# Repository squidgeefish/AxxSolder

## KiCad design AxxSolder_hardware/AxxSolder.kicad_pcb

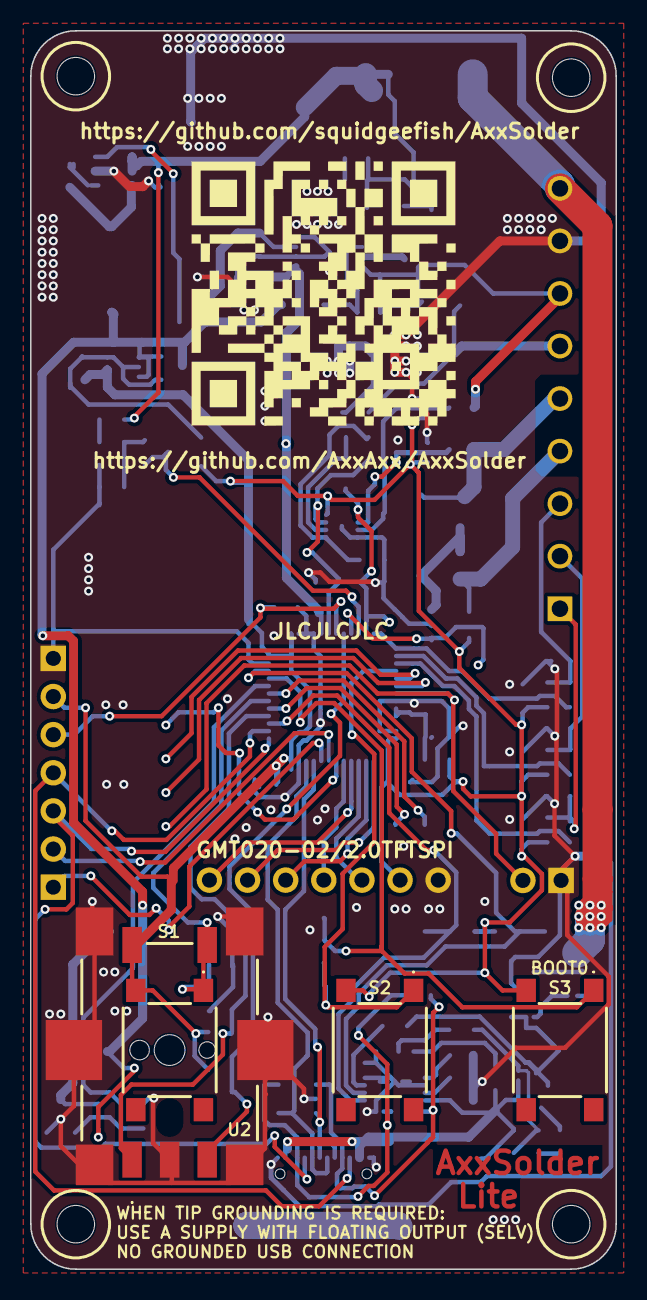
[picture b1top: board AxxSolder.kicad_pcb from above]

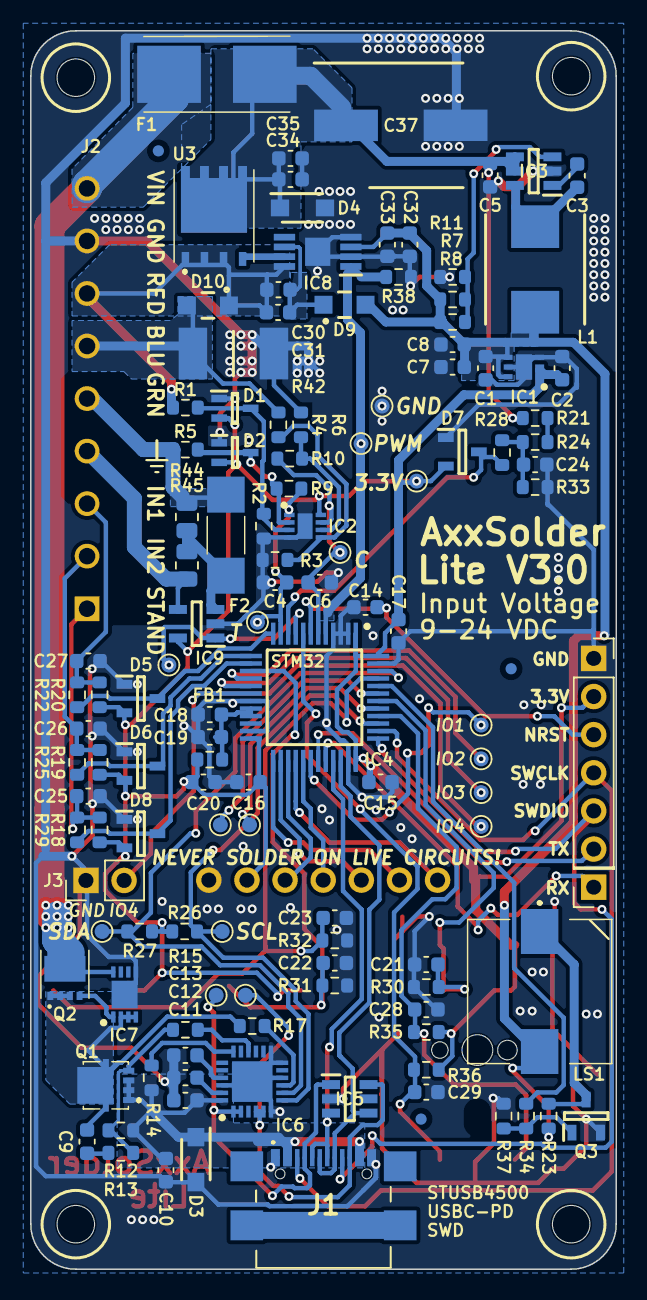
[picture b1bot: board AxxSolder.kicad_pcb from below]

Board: 2 copper layers, 39.0 x 82.5 mm, 137 parts (128 on the bottom side), 68 nets.

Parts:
C1, C2, C5, C7, C8, C10, C11, C12, C13, C19, C20, C30, C31, C32, C34, C35: 10u; C_0603_1608Metric
C3, C9, C14, C15, C16, C17, C18, C21, C22, C23, C24, C25, C26, C27, C28, C29, C33: 100n; C_0603_1608Metric
C4, C6: 1n; C_0603_1608Metric
C37: 220u; CAPAE830X1050N
D1, D2: BAV199WQ-7; SOT65P210X110-3N
D3, D4: SMF4L24AT1G; SODFL3619X98N
D5, D6, D7, D8: BAT54S; SOT95P230X110-3N
D9, D10: PMEG6020ER; PMEG6020ER115
F1: 0154007.DR; 0154100DR
F2: SF-2410FP100W-2; SF2410FP100W2
FB1: BLM18HE601SN1D; R_0603_1608Metric
FID1, FID2, FID3: Fiducial; Fiducial_0.75mm_Mask1.5mm
H1, H2, H3, H4: MountingHole; MountingHole_2.5mm
IC1: TLV76733DRVR; SON65P200X200X80-7N
IC2: OPA2387DSGT; SON50P200X200X80-9N
IC3: LMR54406DBVR; SOT95P280X145-6N
IC4: STM32G431CBT6; QFP50P900X900X160-48N
IC5: TPD4E1U06DBVR; SOT95P280X145-6N
IC6: STUSB4500QTR; QFN50P400X400X100-25N-D
IC7: MAX16171ATA_VY+T; SON50P300X200X80-9N
IC8: LTC4440AHMS8E; SOP65P490X110-9N
IC9: INA281A5QDBVRQ1; SOT95P280X145-5N
J1: USB4110-GF-A; USB4110GFA
J2: 691243110009
J3: TSW-102-07-T-S; PinHeader_1x02_P2.54mm_Vertical
J4: 61300611821; RHDR6W97P0X254_1X6_1574X250X865P
L1: SRP7028CC-150M; INDPM7366X300N
LS1: CMI-9653S-SMT-TR; CMI9653SSMTTR
Q1: STL9P3LLH6; STL20N6F7
Q2: STL10N3LLH5
Q3: 2N7002NXAKR; SOT95P230X110-3N
R1, R5, R14, R17: 1k5; R_0603_1608Metric
R2, R7, R8, R9: 360k; R_0603_1608Metric
R3, R10: 220k; R_0603_1608Metric
R4, R6, R18, R19, R20, R22, R23, R25, R26, R27, R28, R29, R30, R31, R32, R33, R35, R36, R37, R38: 4k7; R_0603_1608Metric
R11, R12, R15, R21, R24: 22k; R_0603_1608Metric
R13, R34: 100; R_0603_1608Metric
R42: 5m; RESC6432X89N
R44: 1M; R_0805_2012Metric
R45: 100m; R_0805_2012Metric
S1, S2, S3: ADTSM644RVTR
TP1, TP2, TP4, TP5, TP6, TP7, TP8, TP14, TP15, TP16: DIAG_TP; TestPoint_Pad_D1.0mm
TP3: 3.3V_TP; TestPoint_Pad_D1.0mm
TP9, TP10: Current_TP; TestPoint_Pad_D1.0mm
TP11: TC_TP; TestPoint_Pad_D1.0mm
TP12: GND_TP; TestPoint_Pad_D1.0mm
TP13: DIAG_TP; PinSocket_1x01_P2.54mm_Vertical
TP17: SW_TP; TestPoint_Pad_D1.0mm
U1: PinHeader_1x07_P2.54mm_Vertical
U2: PEC11J-9215F-S0015; PEC11J9215FS0015
U3: BSC014N04LS

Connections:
+3.3V: C2.1, C15.1, C16.1, C17.1, C20.2, D1.2, D2.2, D5.2 (K), D6.2 (K), D7.2 (K), D8.2 (K), FB1.2, IC1.1 (OUT), IC1.2 (SNS), IC2.8 (V+), IC4.1 (VBAT), IC4.24 (VDD_1), IC4.36 (VDD_2), IC4.48 (VDD_3), IC9.5 (VS), J4.2, R18.1, R19.1, R20.1, R26.2, R27.2, R35.2, R36.1, S1.2, S2.2, S3.2, TP3.1, U1.6 (3V3), U2.D1
+7.5V: C1.1, C7.2, C8.2, C32.1, C33.1, D9.2, IC1.4 (EN), IC1.6 (IN), IC8.3 (VCC), L1.2, LS1.2 (+), R7.2, R8.2, R23.1
/BLUE: D10.2, J2.6, R4.1, R42.1
/BOOST: C30.2, C31.2, D9.1, IC8.6 (BOOST)
/Buzzer: IC4.44 (PB7), R34.1
/CC1: IC5.1 (IO1), IC6.1 (CC1DB), IC6.2 (CC1), J1.A5 (CC1), TP7.1
/CC1_: IC4.43 (PB6), TP1.1
/CC2: IC5.6 (IO4), IC6.4 (CC2), IC6.5 (CC2DB), J1.B5 (CC2), TP8.1
/CC2_: IC4.41 (PB4), TP2.1
/CURRENT: C6.1, IC2.7, IC4.6 (PF1_-_OSC_OUT), R10.1, TP10.1
/ENC_A: C29.1, IC4.8 (PA0), R36.2, U2.C1
/ENC_B: C28.1, IC4.40 (PB3), R35.1, U2.A1
/GREEN: F2.2, J2.5, R5.1, R44.2
/H_sense1: C27.1, J2.3, R20.2, R22.2
/H_sense2: C26.1, J2.2, R19.2, R25.2
/Handle_inp1: D5.3 (common), IC4.12 (PA4), R22.1
/Handle_inp2: D6.3 (common), IC4.13 (PA5), R25.1
/Heater: IC4.5 (PF0_-_OSC_IN), IC8.1 (INP), R38.1, TP17.1
/I_LEAK: IC4.9 (PA1), IC9.1 (OUT), TP9.1
/NRST: C14.2, IC4.7 (PG10_-_NRST), J4.3
/RED: C30.1, C31.1, D10.1, IC8.8 (TS), J2.7, R1.1, U3.1 (S)
/SCL: IC4.39 (PA15), IC6.7 (SCL), R26.1, TP15.1
/SDA: IC4.46 (PB9), IC6.8 (SDA), R27.1, TP16.1
/SPI_CS: IC4.28 (PB14), U1.1 (CS)
/SPI_DC: IC4.25 (PB11), U1.2 (DC)
/SPI_MOSI: IC4.29 (PB15), U1.4 (MOSI)
/SPI_RST: IC4.26 (PB12), U1.3 (RST)
/SPI_SCK: IC4.27 (PB13), U1.5 (SCK)
/SW1: C21.1, IC4.42 (PB5), R30.1, S1.1, U2.E1
/SW2: C22.1, IC4.15 (PA7), R31.1, S2.1
/SW3: C23.1, IC4.45 (PB8-BOOT0), R32.1, S3.1
/SWCLK: IC4.38 (PA14), J1.B8 (SBU2), J4.4
/SWDIO: IC4.37 (PA13), J1.A8 (SBU1), J4.5
/S_sense: C25.1, J2.1, R18.2, R29.2
/Stand_inp: D8.3 (common), IC4.14 (PA6), R29.1
/TC: C4.1, IC2.1, IC4.11 (PA3), R9.1, TP11.1
/USART_RX: IC4.32 (PA10), TP13.1
/USART_TX: IC4.31 (PA9), J4.6
/USB_D+: IC4.34 (PA12), IC5.4 (IO3), J1.A6 (D+), J1.B6 (D+)
/USB_D-: IC4.33 (PA11), IC5.3 (IO2), J1.A7 (D-), J1.B7 (D-)
/USR1: IC4.30 (PA8), TP4.1
/USR2: IC4.16 (PB0), TP6.1
/USR3: IC4.17 (PB1), TP5.1
/USR4: IC4.18 (PB2), J3.2, TP14.1
/VBUS: C10.2, C11.1, D3.1 (K), IC6.24 (VDD), J1.A4 (VBUS), J1.A9 (VBUS), J1.B4 (VBUS), J1.B9 (VBUS), Q1.1 (S), R12.2, R14.2
/VBUS_IN: D7.3 (common), IC4.10 (PA2), R28.2
/VCCA: C18.1, C19.1, FB1.1, IC4.20 (VREF+), IC4.21 (VDDA)
/VDD_IN: F1.2, IC7.8 (OUT), J2.9, Q2.5 (D)
/VDD_IN_USBCPD: C9.2, IC7.2 (SRC), IC7.3 (IN), IC7.4 (EN), Q1.5 (D), Q2.1 (S), R17.2
Earth: IC9.4 (IN-), J2.4, R45.1
GND: C1.2, C2.2, C4.2, C5.1, C6.2, C7.1, C8.1, C10.1, C11.2, C12.2, C13.2, C14.1, C15.2, C16.2, C17.2, C18.2, C19.2, C20.1, C21.2, C22.2, C23.2, C24.2, C25.2, C26.2, C27.2, C28.2, C29.2, C32.2, C33.2, C34.1, C35.1, C37.2, D1.1, D2.1, D3.2 (A), D4.2 (A), D5.1 (A), D6.1 (A), D7.1 (A), D8.1 (A), IC1.3 (GND_1), IC1.5 (GND_2), IC1.7 (EP), IC2.4 (V-), IC2.9 (THERMAL_PAD), IC3.2 (GND), IC4.2 (PC13), IC4.3 (PC14_-_OSC32_IN), IC4.4 (PC15_-_OSC32_OUT), IC4.19 (VSSA), IC4.23 (VSS_1), IC4.35 (VSS_2), IC4.47 (VSS_3), IC5.2 (GND), IC6.6 (RESET), IC6.10 (GND), IC6.12 (ADDR0), IC6.13 (ADDR1), IC6.22 (VSYS), IC6.25 (EP), IC7.5 (GND), IC7.9 (EP), IC8.2 (GND_1), IC8.4 (GND_2), IC8.9 (EP), IC9.2 (GND), J1.A1 (GND), J1.A12 (GND), J1.B1 (GND), J1.B12 (GND), J2.8, J3.1, J4.1, Q3.2 (S), R2.2, R3.2, R6.2, R11.1, R30.2, R31.2, R32.2, R33.2, R37.2, R38.2, R42.2, TP12.1, U1.7 (GND), U2.B1, U2.MP
unnamed: C9.1, R13.2
unnamed: C24.1, R24.1, R28.1, R33.1
unnamed: D1.3, IC2.3 (+), R1.2, R2.1
unnamed: D2.3, IC2.2 (-), R5.2, R9.2
unnamed: IC2.5 (+), R3.1, R4.2
unnamed: IC2.6 (-), R6.1, R10.2
unnamed: C3.1, IC3.1 (CB)
unnamed: IC3.3 (FB), R7.1, R8.1, R11.2
unnamed: C3.2, IC3.6 (SW), L1.1
unnamed: IC7.1 (GATE), Q2.4 (G)
unnamed: IC8.7 (TG), U3.9 (G)
unnamed: F2.1, IC9.3 (IN+), R44.1, R45.2
unnamed: LS1.1 (-), Q3.3 (D), R23.2
unnamed: Q1.4 (G), R12.1, R13.1, R15.2
unnamed: Q3.1 (G), R34.2, R37.1
unnamed: R21.1, R24.2
VDD: C5.2, C34.2, C35.2, C37.1, D4.1 (K), F1.1, IC3.4 (EN), IC3.5 (VIN), R21.2, U3.10 (D)

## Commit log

2024-05-25 Add GMT020-02 model
2024-05-25 Create Lite version of board
    Mark all USB-C components as DNP (except I2C pullups)
    Swap LCD footprint from Adafruit 4311 to commodity GMT020-02 LCD
2024-05-25 Finish Lite modifications
    Fix upper mounting holes (no longer align with display; now aligned to PCB)
    Add GitHub link for licensing purposes (I think this is necesssary for GPL)
2025-01-27 Change SPI2 clock polarity and default orientation for GMT020-02 ST7789V breakout
2025-01-27 Export .bin file after build
